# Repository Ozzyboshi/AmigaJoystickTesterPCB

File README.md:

# AmigaJoystickTesterPCB

Simple PCB for testing a 9pin Amiga Joystick.

Components:
* Resistors 220 OHM
* Leds 2V - 20mA
* D-SUB 9 pin PCB Male Connector
* Micro USB Type B Female 5 Pin Connector plug adapter

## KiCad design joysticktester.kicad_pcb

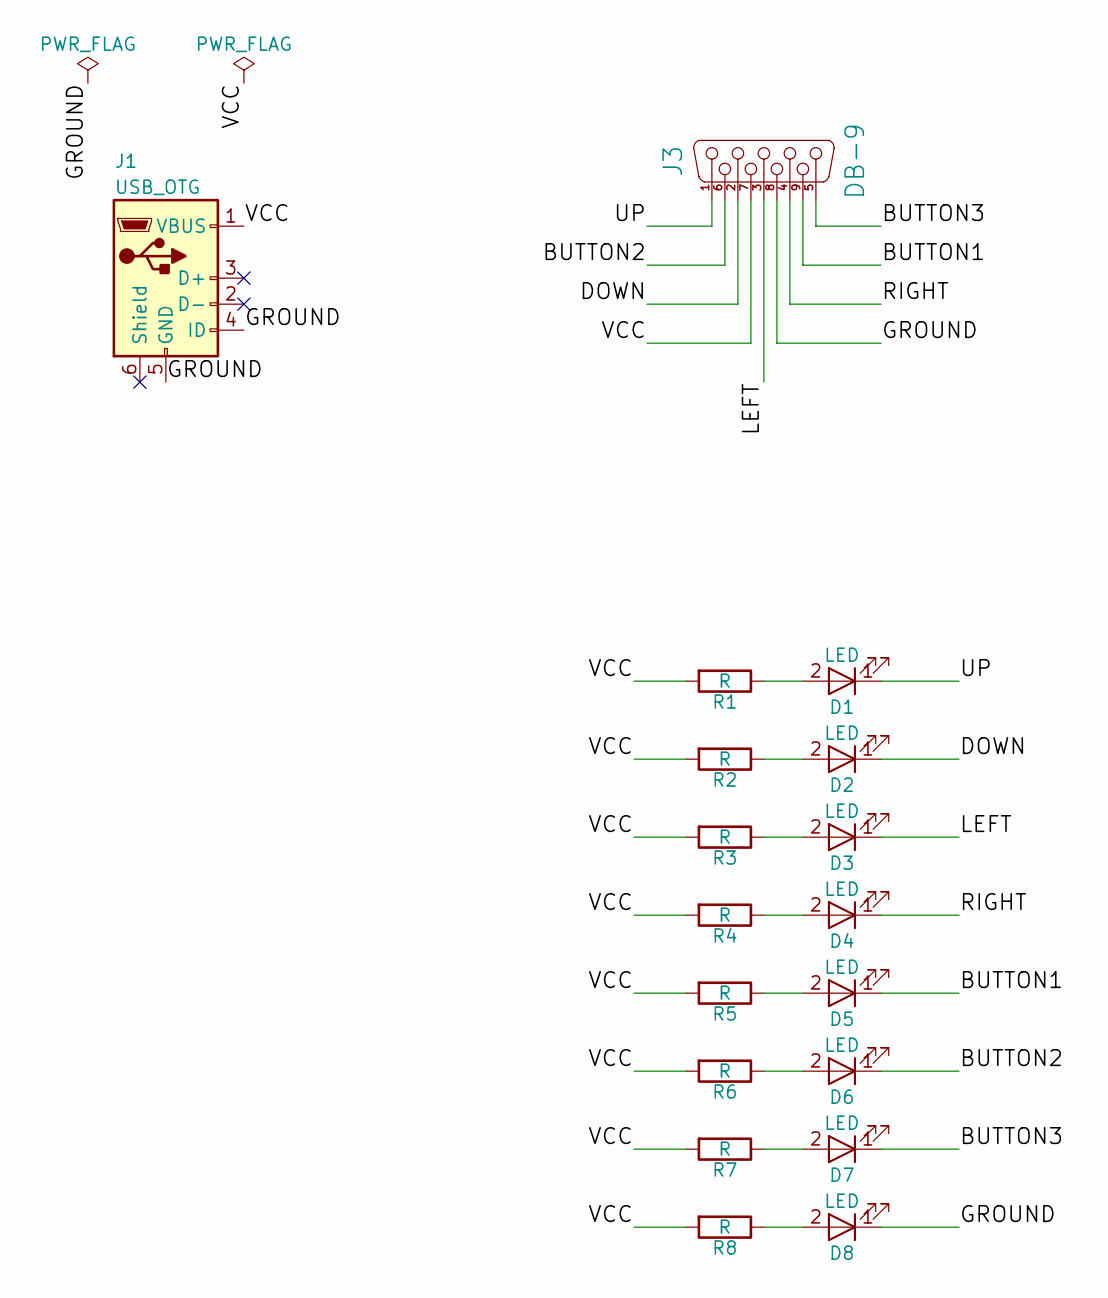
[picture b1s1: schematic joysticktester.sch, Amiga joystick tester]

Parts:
D1, D2, D3, D4, D5, D6, D7, D8: LED; LED_D3.0mm
J1: USB_OTG; USB_Micro-B
J3: DB-9; DB_9M
R1, R2, R3, R4, R5, R6, R7, R8: R; R_Axial_DIN0309_L9.0mm_D3.2mm_P20.32mm_Horizontal

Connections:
/BUTTON1: D5.1 (K), J3.9
/BUTTON2: D6.1 (K), J3.6
/BUTTON3: D7.1 (K), J3.5
/DOWN: D2.1 (K), J3.2
/GROUND: D8.1 (K), J1.4 (ID), J1.5 (GND), J3.8
/LEFT: D3.1 (K), J3.3
/RIGHT: D4.1 (K), J3.4
/UP: D1.1 (K), J3.1
/VCC: J1.1 (VBUS), J3.7, R1.2, R2.2, R3.2, R4.2, R5.2, R6.2, R7.2, R8.2
unnamed: D1.2 (A), R1.1
unnamed: D2.2 (A), R2.1
unnamed: D3.2 (A), R3.1
unnamed: D4.2 (A), R4.1
unnamed: D5.2 (A), R5.1
unnamed: D6.2 (A), R6.1
unnamed: D7.2 (A), R7.1
unnamed: D8.2 (A), R8.1

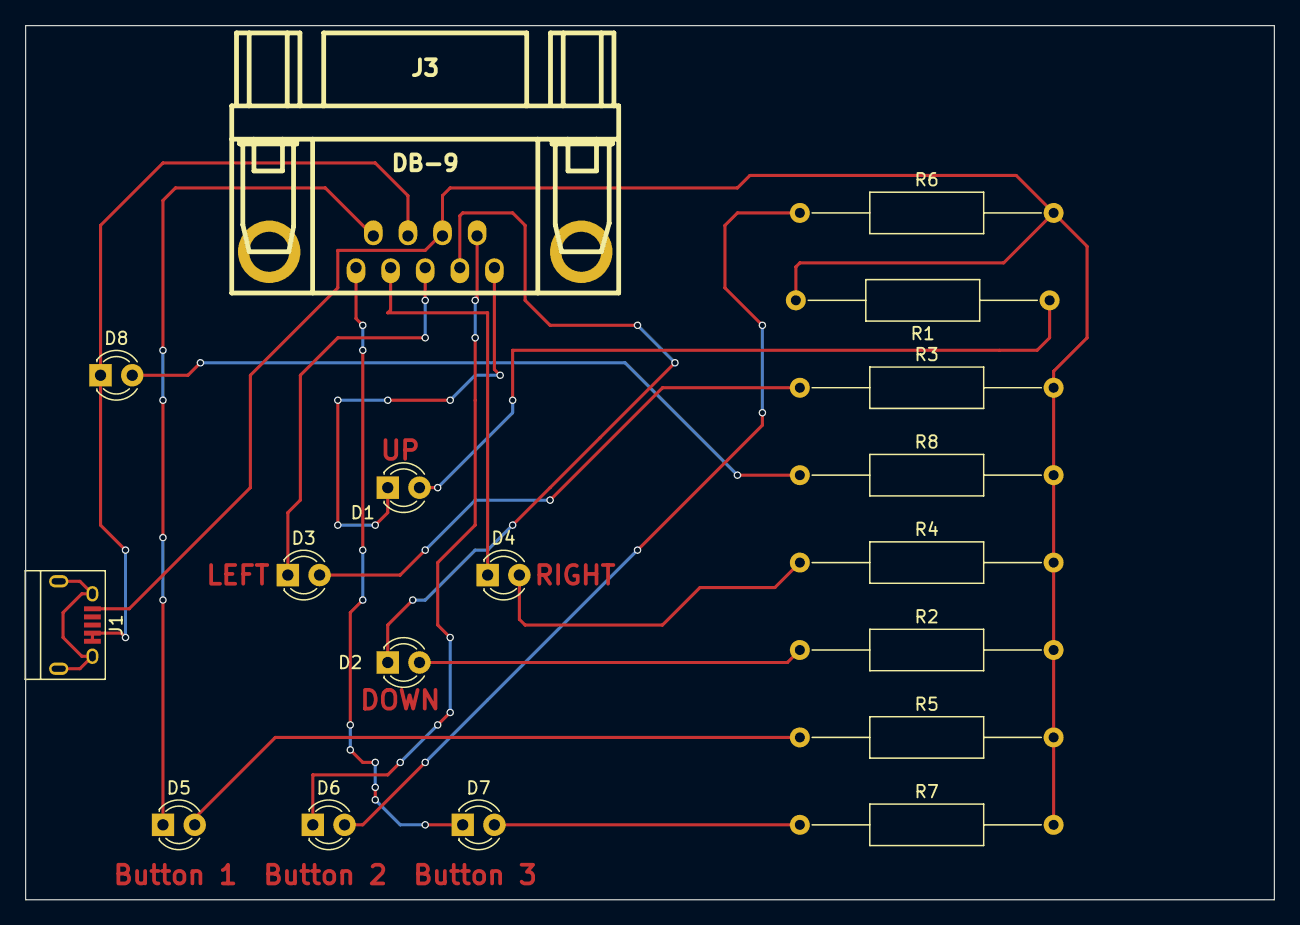
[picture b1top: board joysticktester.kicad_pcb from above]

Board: 2 copper layers, 100.0 x 70.0 mm, 18 parts (0 on the bottom side), 17 nets.

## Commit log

2018-02-24 fix led connection
2018-02-24 image of the pcb added
2018-02-24 rotated usb connector
2018-02-25 new db9 connector
2018-02-25 deleted old jpeg image
2018-02-25 new silk back
2018-02-28 added btn desc
2018-02-28 new img
2018-03-04 change db9 direction
